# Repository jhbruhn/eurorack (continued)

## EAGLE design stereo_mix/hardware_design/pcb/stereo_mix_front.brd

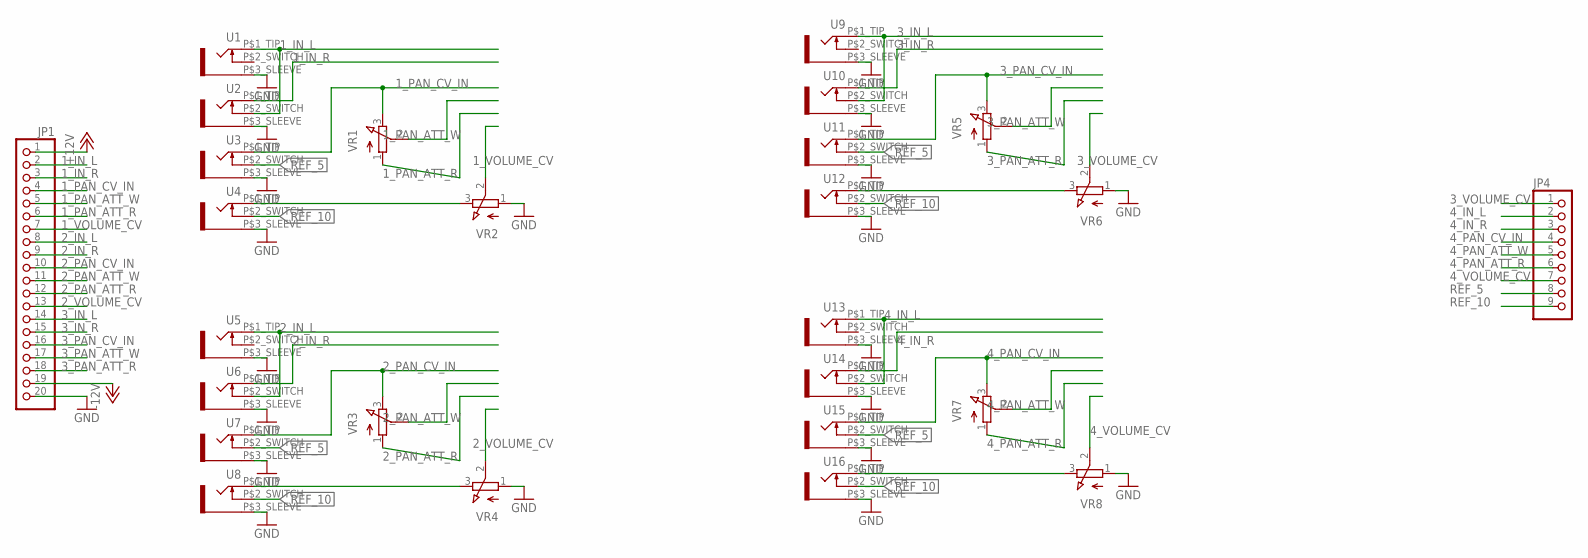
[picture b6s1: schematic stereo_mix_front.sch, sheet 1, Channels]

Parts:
JP1: PINHD-1X20; 1X20
JP4: PINHD-1X9; 1X09
U1, U2, U3, U4, U5, U6, U7, U8, U9, U10, U11, U12, U13, U14, U15, U16: WQP-PJ301M-12_JACK
VR1, VR2, VR3, VR4, VR5, VR6, VR7, VR8: 9MM_SNAP-IN_POT_; 9MM_SNAP-IN_POT

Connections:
1_IN_L: JP1.2, U1.P$1_TIP (2), U2.P$2_SWITCH (3)
1_IN_R: JP1.3, U2.P$1_TIP (2)
1_PAN_ATT_R: JP1.6, VR1.1 (A)
1_PAN_ATT_W: JP1.5, VR1.2 (S)
1_PAN_CV_IN: JP1.4, U3.P$1_TIP (2), VR1.3 (E)
1_VOLUME_CV: JP1.7, VR2.2 (S)
2_IN_L: JP1.8, U5.P$1_TIP (2), U6.P$2_SWITCH (3)
2_IN_R: JP1.9, U6.P$1_TIP (2)
2_PAN_ATT_R: JP1.12, VR3.1 (A)
2_PAN_ATT_W: JP1.11, VR3.2 (S)
2_PAN_CV_IN: JP1.10, U7.P$1_TIP (2), VR3.3 (E)
2_VOLUME_CV: JP1.13, VR4.2 (S)
3_IN_L: JP1.14, U9.P$1_TIP (2), U10.P$2_SWITCH (3)
3_IN_R: JP1.15, U10.P$1_TIP (2)
3_PAN_ATT_R: JP1.18, VR5.1 (A)
3_PAN_ATT_W: JP1.17, VR5.2 (S)
3_PAN_CV_IN: JP1.16, U11.P$1_TIP (2), VR5.3 (E)
3_VOLUME_CV: JP4.1, VR6.2 (S)
4_IN_L: JP4.2, U13.P$1_TIP (2), U14.P$2_SWITCH (3)
4_IN_R: JP4.3, U14.P$1_TIP (2)
4_PAN_ATT_R: JP4.6, VR7.1 (A)
4_PAN_ATT_W: JP4.5, VR7.2 (S)
4_PAN_CV_IN: JP4.4, U15.P$1_TIP (2), VR7.3 (E)
4_VOLUME_CV: JP4.7, VR8.2 (S)
+12V: JP1.1
-12V: JP1.19
GND: JP1.20, U1.P$3_SLEEVE (1), U2.P$3_SLEEVE (1), U3.P$3_SLEEVE (1), U4.P$3_SLEEVE (1), U5.P$3_SLEEVE (1), U6.P$3_SLEEVE (1), U7.P$3_SLEEVE (1), U8.P$3_SLEEVE (1), U9.P$3_SLEEVE (1), U10.P$3_SLEEVE (1), U11.P$3_SLEEVE (1), U12.P$3_SLEEVE (1), U13.P$3_SLEEVE (1), U14.P$3_SLEEVE (1), U15.P$3_SLEEVE (1), U16.P$3_SLEEVE (1), VR2.1 (A), VR4.1 (A), VR6.1 (A), VR8.1 (A); also elsewhere on the board
unnamed: U8.P$1_TIP (2), VR4.3 (E)
unnamed: U4.P$1_TIP (2), VR2.3 (E)
unnamed: U12.P$1_TIP (2), VR6.3 (E)
unnamed: U16.P$1_TIP (2), VR8.3 (E)
REF_5: JP4.8, U3.P$2_SWITCH (3), U7.P$2_SWITCH (3), U11.P$2_SWITCH (3), U15.P$2_SWITCH (3)
REF_10: JP4.9, U4.P$2_SWITCH (3), U8.P$2_SWITCH (3), U12.P$2_SWITCH (3), U16.P$2_SWITCH (3)

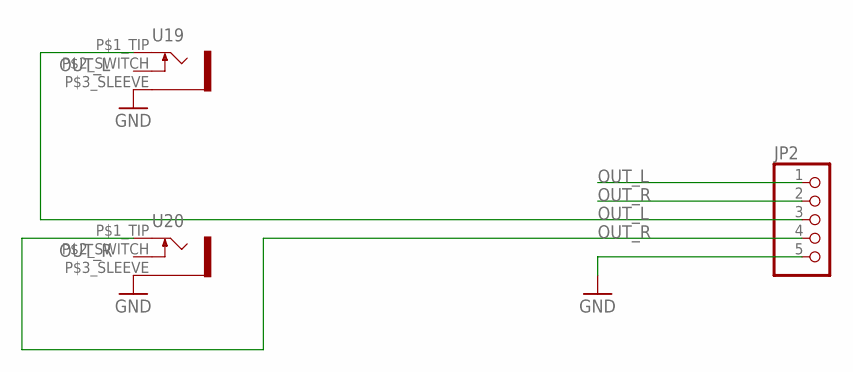
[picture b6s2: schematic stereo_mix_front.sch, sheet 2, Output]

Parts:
JP2: PINHD-1X5; 1X05
U19, U20: WQP-PJ301M-12_JACK

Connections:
GND: JP2.5, U19.P$3_SLEEVE (1), U20.P$3_SLEEVE (1); also elsewhere on the board
OUT_L: JP2.1, JP2.3, U19.P$1_TIP (2)
OUT_R: JP2.2, JP2.4, U20.P$1_TIP (2)

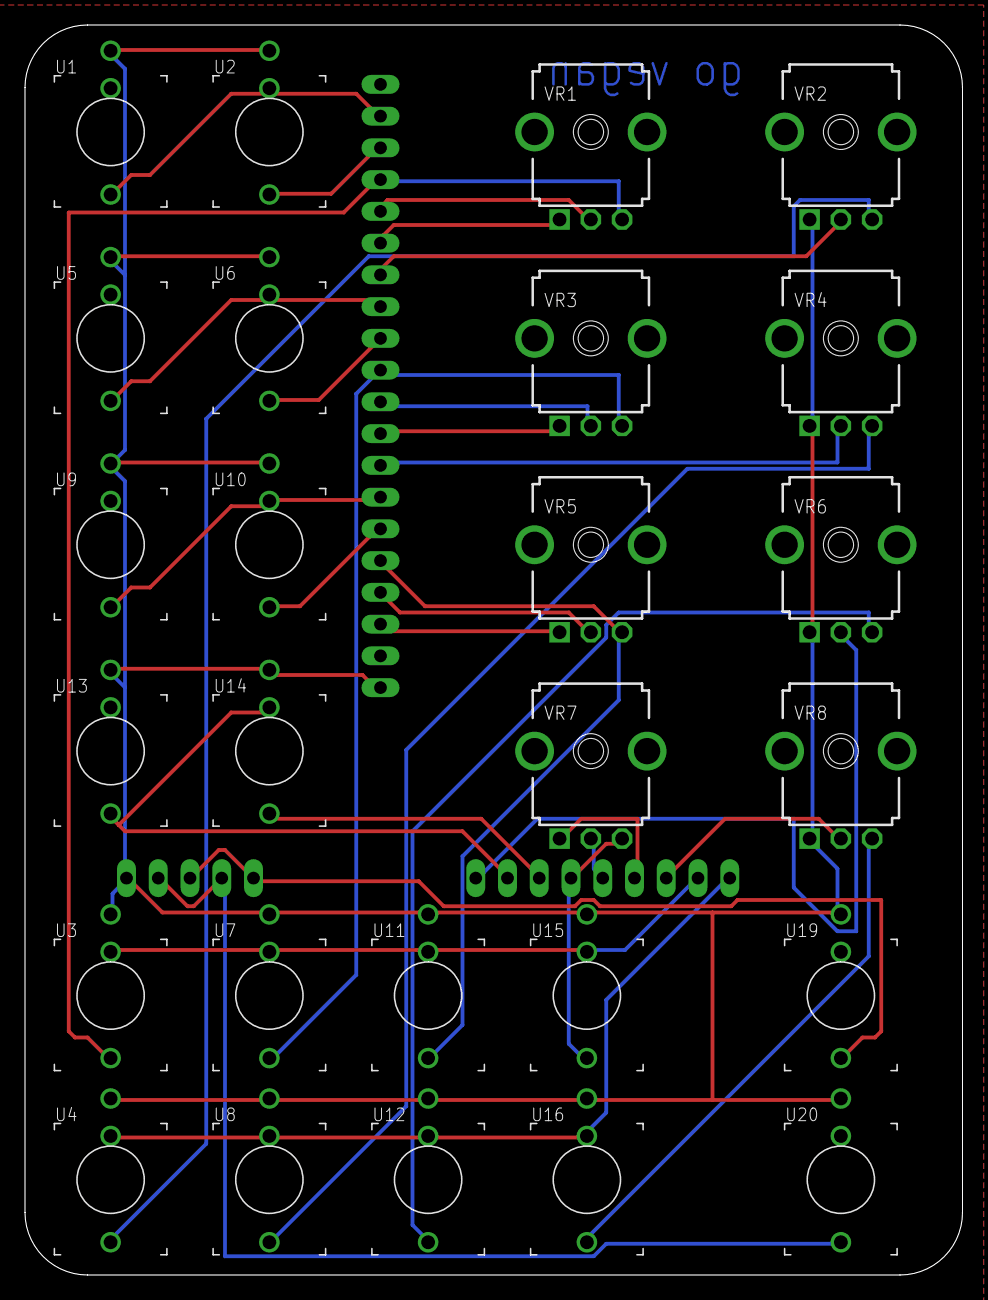
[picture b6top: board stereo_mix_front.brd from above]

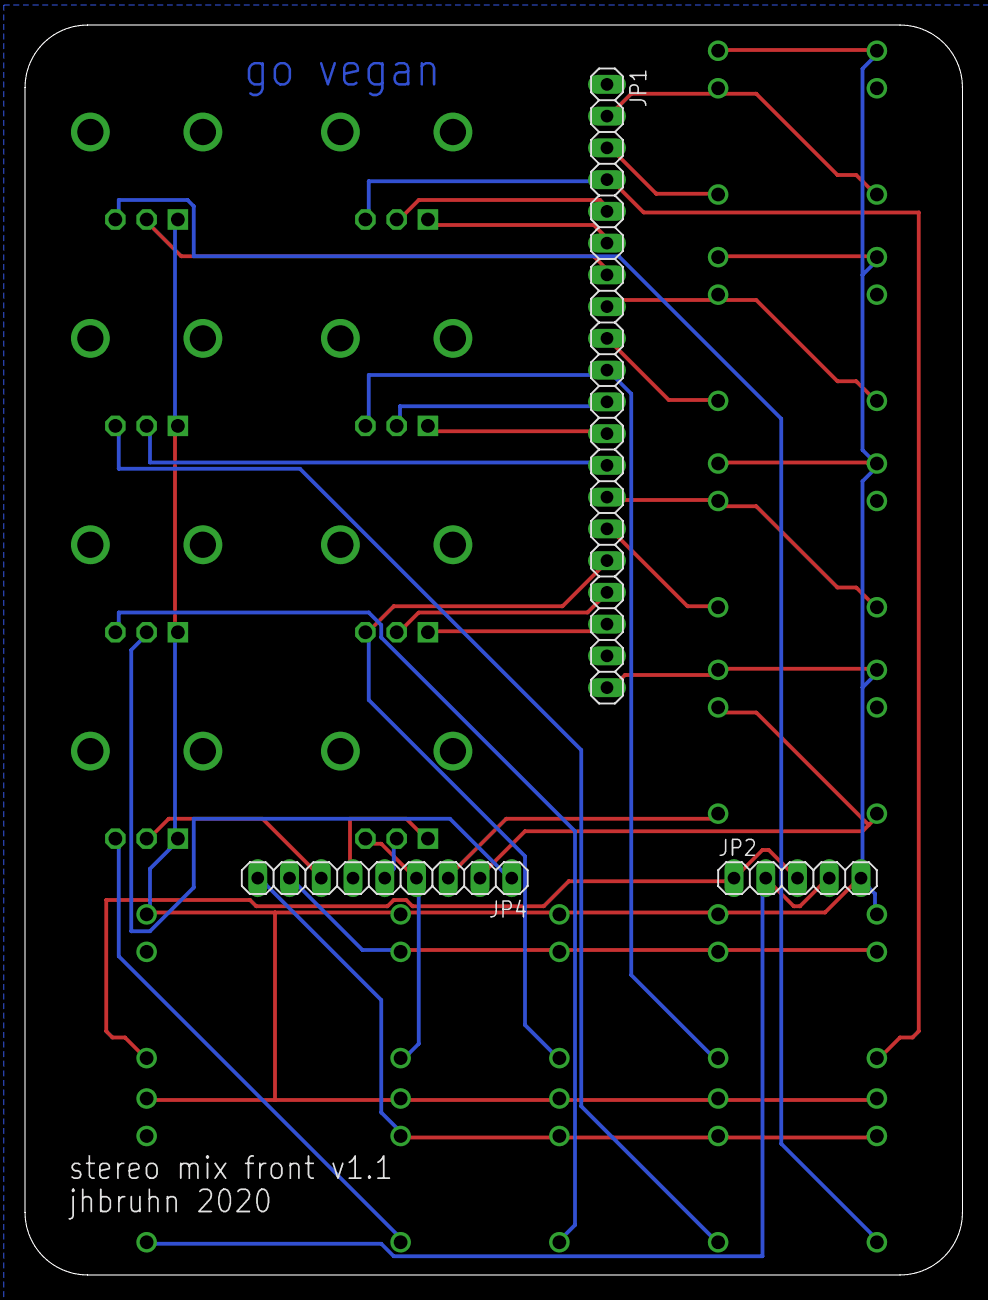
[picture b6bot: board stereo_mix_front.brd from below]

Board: 2 copper layers, 75.0 x 100.0 mm, 29 parts (3 on the bottom side), 33 nets.

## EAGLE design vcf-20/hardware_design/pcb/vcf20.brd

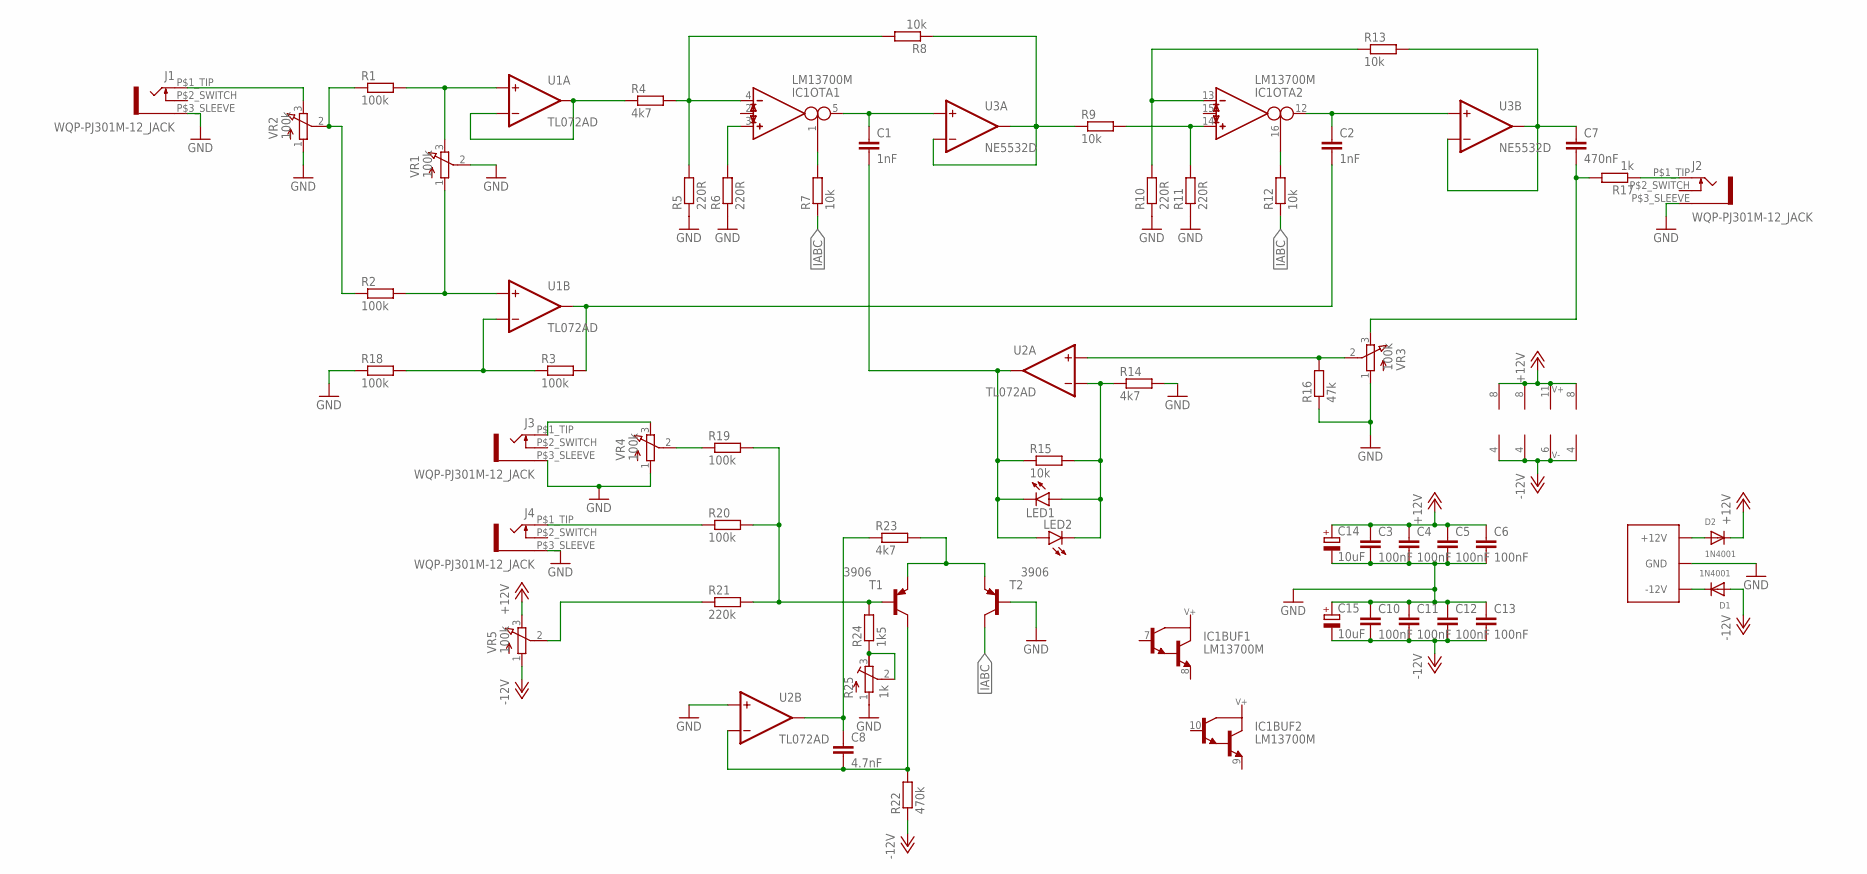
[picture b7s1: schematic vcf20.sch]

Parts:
C1, C2: 1nF; C0402
C3, C4, C5, C6, C10, C11, C12, C13: 100nF; C0402
C7: 470nF; C0402
C8: 4.7nF; C0402
C9: EURO_POWER_LOCKFAT-LOCK; EURO_PWR_HEADER_LOCK
C14, C15: 10uF; PANASONIC_C
D1, D2: 1N4001; SMADIODE
IC1: LM13700M; SO16
J1, J2, J3, J4: WQP-PJ301M-12_JACK
LED1, LED2: LEDSML0603; SML0603
R1, R2, R3, R18, R19, R20: 100k; R0402
R4, R14, R23: 4k7; R0402
R5, R6, R10, R11: 220R; R0402
R7, R8, R9, R12, R13, R15: 10k; R0402
R16: 47k; R0402
R17: 1k; R0402
R21: 220k; R0402
R22: 470k; R0402
R24: 1k5; R0402
R25: 1k; RTRIM64W
T1, T2: 3906; SOT23-BEC
U1, U2: TL072AD; SOIC8
U3: NE5532D; SOIC8
VR1, VR2, VR3, VR4, VR5: 100k; 9MM_SNAP-IN_POT

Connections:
+12V: C3.1, C4.1, C5.1, C6.1, C14.+, D2.C, IC1.11 (V+), U1.8 (V+), U2.8 (V+), U3.8 (V+), VR5.3 (E)
-12V: C10.2, C11.2, C12.2, C13.2, C15.-, D1.A, IC1.6 (V-), R22.1, U1.4 (V-), U2.4 (V-), U3.4 (V-), VR5.1 (A)
GND: C3.2, C4.2, C5.2, C6.2, C9.GND1 (GND), C9.GND2 (GND), C9.GND3 (GND), C9.GND4 (GND), C9.GND5 (GND), C9.GND6 (GND), C10.1, C11.1, C12.1, C13.1, C14.-, C15.+, J1.P$3_SLEEVE (1), J2.P$3_SLEEVE (1), J3.P$3_SLEEVE (1), J4.P$3_SLEEVE (1), R5.1, R6.1, R10.1, R11.1, R14.2, R16.1, R18.1, R25.1 (A), T2.B, U2.5 (+IN), VR1.2 (S), VR2.1 (A), VR3.1 (A), VR4.1 (A)
IABC: R7.1, R12.1, T2.C
unnamed: IC1.4 (IN_N), R4.2, R5.2, R8.2
unnamed: IC1.3 (IN_P), R6.2
unnamed: IC1.1 (I_BIAS), R7.2
unnamed: IC1.14 (IN_P), R9.2, R11.2
unnamed: IC1.16 (I_BIAS), R12.2
unnamed: IC1.13 (IN_N), R10.2, R13.1
unnamed: R8.1, R9.1, U3.1 (OUT), U3.2 (-IN)
unnamed: C1.1, IC1.5 (OUT), U3.3 (+IN)
unnamed: R3.1, R18.2, U1.6 (-IN)
unnamed: C7.1, R13.2, U3.6 (-IN), U3.7 (OUT)
unnamed: C2.1, IC1.12 (OUT), U3.5 (+IN)
unnamed: C2.2, R3.2, U1.7 (OUT)
unnamed: R1.2, U1.3 (+IN), VR1.3 (E)
unnamed: R2.2, U1.5 (+IN), VR1.1 (A)
unnamed: C7.2, R17.2, VR3.3 (E)
unnamed: R4.1, U1.1 (OUT), U1.2 (-IN)
unnamed: R1.1, R2.1, VR2.2 (S)
unnamed: LED1.A, LED2.C, R14.1, R15.2, U2.2 (-IN)
unnamed: J1.P$1_TIP (2), VR2.3 (E)
unnamed: R16.2, U2.3 (+IN), VR3.2 (S)
unnamed: C1.2, LED1.C, LED2.A, R15.1, U2.1 (OUT)
unnamed: J2.P$1_TIP (2), R17.1
unnamed: R24.1, R25.2 (S), R25.3 (E)
unnamed: C8.2, R22.2, T1.C, U2.6 (-IN)
unnamed: J3.P$1_TIP (2), VR4.3 (E)
unnamed: J4.P$1_TIP (2), R20.1
unnamed: R19.1, VR4.2 (S)
unnamed: R21.1, VR5.2 (S)
unnamed: R19.2, R20.2, R21.2, R24.2, T1.B
unnamed: C9.POS1 (+12V), C9.POS2 (+12V), D2.A
unnamed: R23.2, T1.E, T2.E
unnamed: C8.1, R23.1, U2.7 (OUT)
unnamed: C9.NEG1 (-12V), C9.NEG2 (-12V), D1.C

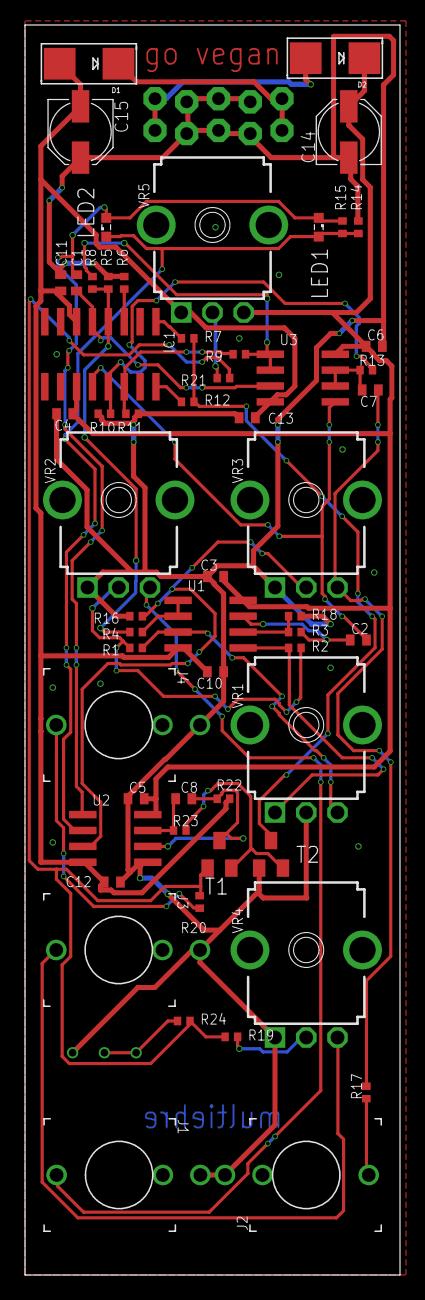
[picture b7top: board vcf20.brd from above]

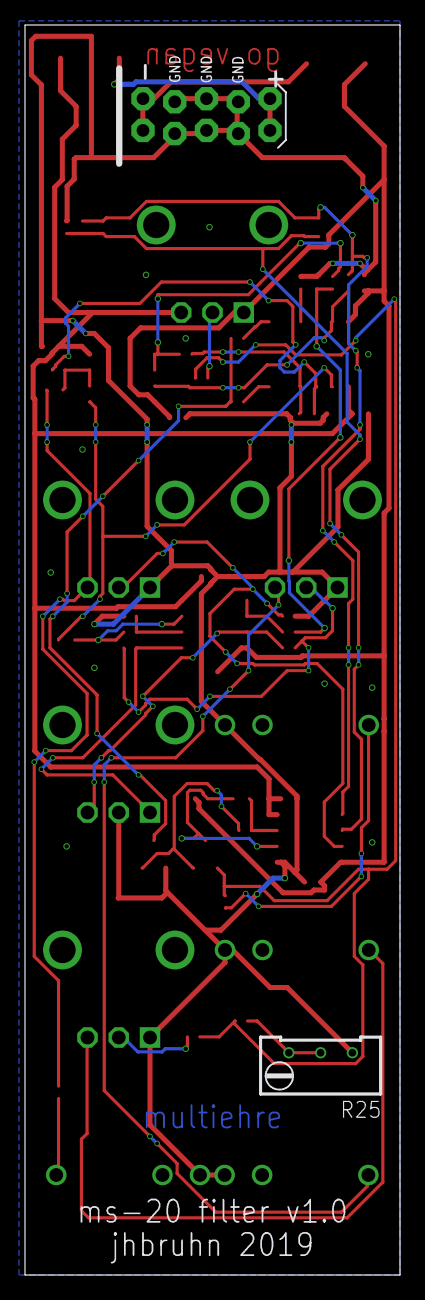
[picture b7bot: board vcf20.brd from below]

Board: 2 copper layers, 30.0 x 100.0 mm, 59 parts (2 on the bottom side), 37 nets.

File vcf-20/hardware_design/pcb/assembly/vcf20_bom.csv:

"Comment","Designator","Footprint","LCSC Part #","LCSC Part Type"
"","LED1, LED2","SML0603","",""
"100k","VR1, VR2, VR3, VR4, VR5","9MM_SNAP-IN_POT","",""
"100k","R1, R2, R3, R18, R19, R20","0402_R","",""
"100nF","C3, C4, C5, C6, C10, C11, C12, C13","0402_C","",""
"10k","R7, R8, R9, R12, R13, R15","0402_R","",""
"10uF","C14, C15","PANASONIC_C","",""
"1N4001","D1, D2","SMADIODE","",""
"1k","R17","0402_R","",""
"1k","R25","RTRIM64W","",""
"1k5","R24","0402_R","",""
"1nF","C1, C2","0402_C","",""
"220R","R5, R6, R10, R11","0402_R","",""
"220k","R21","0402_R","",""
"3904","T1, T2","SOT23-BEC","",""
"4.7nF","C8","0402_C","",""
"470k","R22","0402_R","",""
"470nF","C7","0402_C","",""
"47k","R16","0402_R","",""
"4k7","R4, R14, R23","0402_R","",""
"EURO_POWER_LOCKFAT-LOCK","C9","EURO_PWR_HEADER_LOCK","",""
"LM13700M","IC1","SO16","",""
"NE5532D","U3","SOIC8","",""
"TL072AD","U1, U2","SOIC8","",""
"WQP-PJ301M-12_JACK","J1, J2, J3, J4","WQP-PJ301M-12_JACK","",""

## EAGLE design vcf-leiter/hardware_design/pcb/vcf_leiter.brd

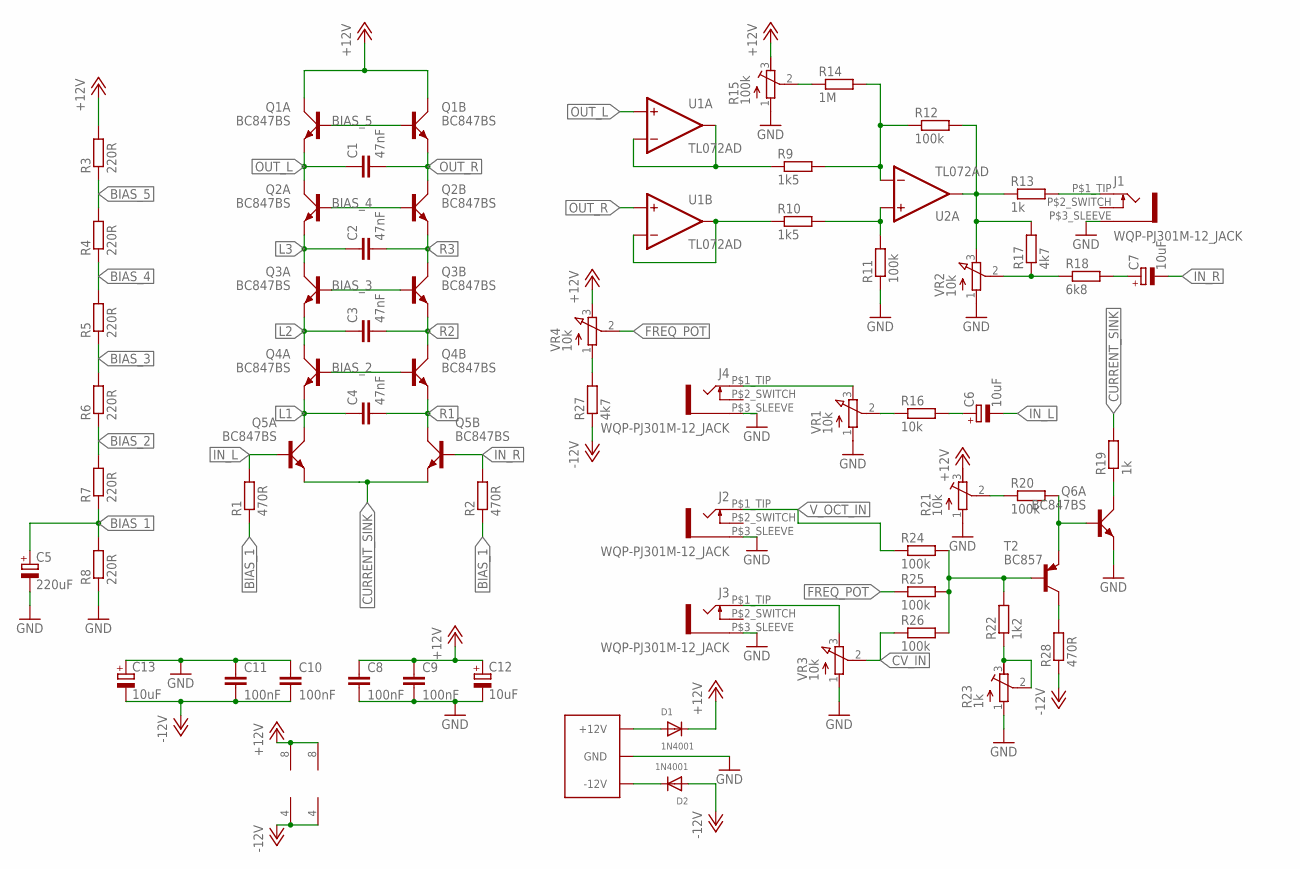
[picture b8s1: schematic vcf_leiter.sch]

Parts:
C1, C2, C3, C4: 47nF; C0402
C5: 220uF; PANASONIC_C
C6, C7, C12, C13: 10uF; PANASONIC_C
C8, C9, C10, C11: 100nF; C0402
C14: EURO_POWER_LOCKFAT-LOCK; EURO_PWR_HEADER_LOCK
D1, D2: 1N4001; SMADIODE
J1, J2, J3, J4: WQP-PJ301M-12_JACK
Q1, Q2, Q3, Q4, Q5, Q6: BC847BS; SOT363_PHILIPS
R1, R2, R28: 470R; R0402
R3, R4, R5, R6, R7, R8: 220R; R0402
R9, R10: 1k5; R0402
R11, R12, R20, R24, R25, R26: 100k; R0402
R13, R19: 1k; R0402
R14: 1M; R0402
R15: 100k; RTRIM64W
R16: 10k; R0402
R17, R27: 4k7; R0402
R18: 6k8; R0402
R21: 10k; RTRIM64W
R22: 1k2; R0402
R23: 1k; RTRIM64W
T2: BC857; SOT23-BEC
U1, U2: TL072AD; SOIC8
VR1, VR2, VR3, VR4: 10k; 9MM_SNAP-IN_POT

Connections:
+12V: C8.1, C9.1, C12.+, D1.C, Q1.3 (C), Q1.6 (C), R3.2, R15.3 (E), R21.3 (E), U1.8 (V+), U2.8 (V+), VR4.3 (E)
-12V: C10.2, C11.2, C13.-, D2.A, R27.1, R28.1, U1.4 (V-), U2.4 (V-)
BIAS_1: C5.+, R1.1, R2.1, R7.1, R8.2
BIAS_2: Q4.2 (B), Q4.5 (B), R6.1, R7.2
BIAS_3: Q3.2 (B), Q3.5 (B), R5.1, R6.2
BIAS_4: Q2.2 (B), Q2.5 (B), R4.1, R5.2
BIAS_5: Q1.2 (B), Q1.5 (B), R3.1, R4.2
CURRENT_SINK: Q5.1 (E), Q5.4 (E), R19.2
CV_IN: R26.1, VR3.2 (S)
FREQ_POT: R25.1, VR4.2 (S)
GND: C5.-, C8.2, C9.2, C10.1, C11.1, C12.-, C13.+, C14.GND1 (GND), C14.GND2 (GND), C14.GND3 (GND), C14.GND4 (GND), C14.GND5 (GND), C14.GND6 (GND), J1.P$3_SLEEVE (1), J2.P$3_SLEEVE (1), J3.P$3_SLEEVE (1), J4.P$3_SLEEVE (1), Q6.1 (E), R8.1, R11.1, R15.1 (A), R21.1 (A), R23.1 (A), VR1.1 (A), VR2.1 (A), VR3.1 (A)
IN_L: C6.-, Q5.2 (B), R1.2
IN_R: C7.-, Q5.5 (B), R2.2
L1: C4.1, Q4.1 (E), Q5.6 (C)
L2: C3.1, Q3.1 (E), Q4.6 (C)
L3: C2.1, Q2.1 (E), Q3.6 (C)
unnamed: R9.1, U1.1 (OUT), U1.2 (-IN)
unnamed: R10.1, U1.6 (-IN), U1.7 (OUT)
unnamed: R10.2, R11.2, U2.3 (+IN)
unnamed: R9.2, R12.1, R14.2, U2.2 (-IN)
unnamed: J4.P$1_TIP (2), VR1.3 (E)
unnamed: R12.2, R13.1, R17.2, U2.1 (OUT), VR2.3 (E)
unnamed: R14.1, R15.2 (S)
unnamed: R16.1, VR1.2 (S)
unnamed: C6.+, R16.2
unnamed: J1.P$1_TIP (2), R13.2
unnamed: R17.1, R18.1, VR2.2 (S)
unnamed: C7.+, R18.2
unnamed: Q6.2 (B), R20.2, T2.E
unnamed: J3.P$1_TIP (2), VR3.3 (E)
unnamed: Q6.6 (C), R19.1
unnamed: R20.1, R21.2 (S)
unnamed: R22.2, R24.2, R25.2, R26.2, T2.B
unnamed: R22.1, R23.2 (S), R23.3 (E)
unnamed: R27.2, VR4.1 (A)
unnamed: R28.2, T2.C
unnamed: C14.POS1 (+12V), C14.POS2 (+12V), D1.A
unnamed: C14.NEG1 (-12V), C14.NEG2 (-12V), D2.C
OUT_L: C1.1, Q1.1 (E), Q2.6 (C), U1.3 (+IN)
OUT_R: C1.2, Q1.4 (E), Q2.3 (C), U1.5 (+IN)
R1: C4.2, Q4.4 (E), Q5.3 (C)
R2: C3.2, Q3.4 (E), Q4.3 (C)
R3: C2.2, Q2.4 (E), Q3.3 (C)
V_OCT_IN: J2.P$1_TIP (2), R24.1

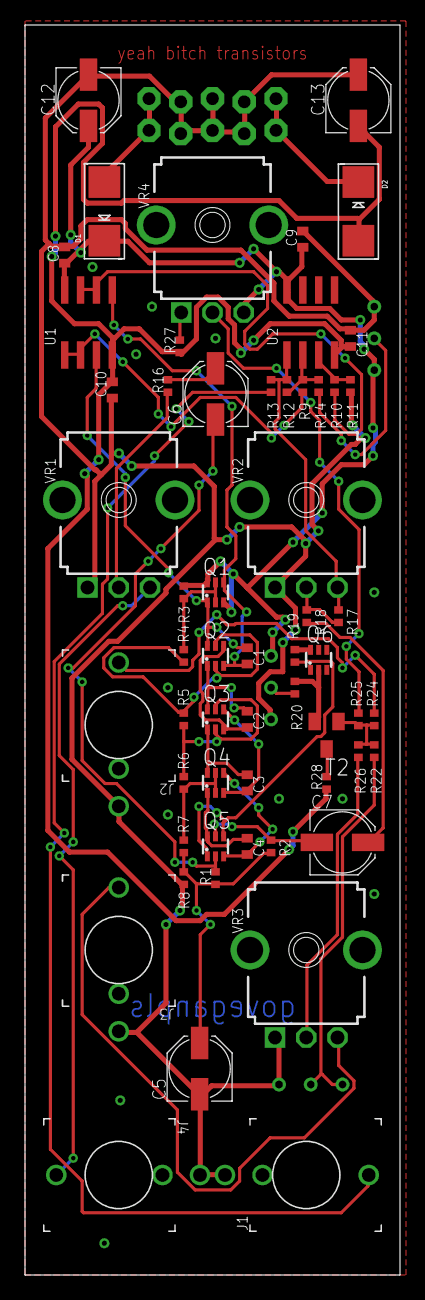
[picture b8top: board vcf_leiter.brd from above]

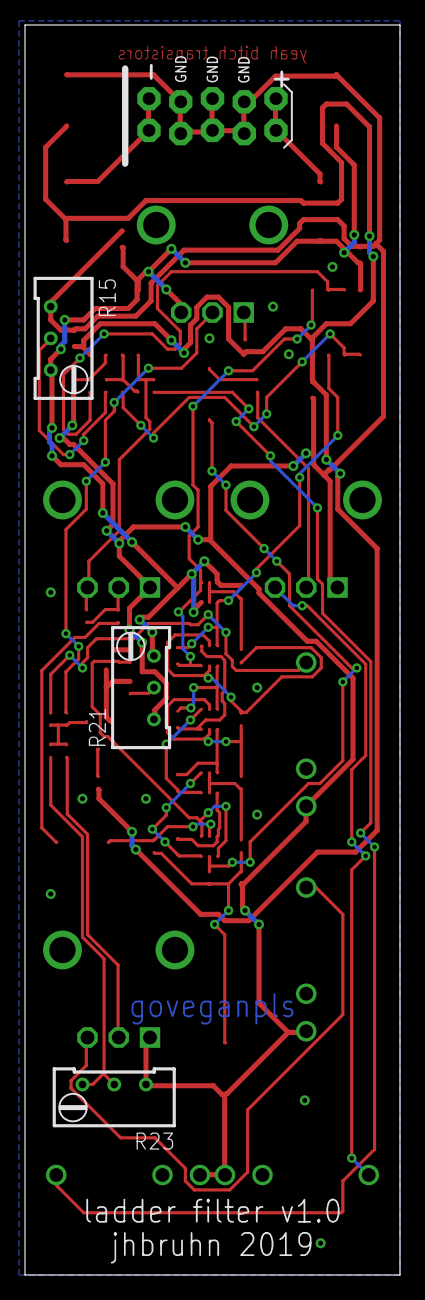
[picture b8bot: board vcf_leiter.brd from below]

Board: 2 copper layers, 30.0 x 100.0 mm, 61 parts (4 on the bottom side), 44 nets.

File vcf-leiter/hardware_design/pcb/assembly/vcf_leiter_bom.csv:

"Comment","Designator","Footprint","LCSC Part #","LCSC Part Type"
"100k","R11, R12, R20, R24, R25, R26","0402_R","",""
"100k","R15","RTRIM64W","",""
"100nF","C8, C9, C10, C11","0402_C","",""
"10k","VR1, VR2, VR3, VR4","9MM_SNAP-IN_POT","",""
"10k","R16","0402_R","",""
"10k","R21","RTRIM64W","",""
"10uF","C6, C7, C12, C13","PANASONIC_C","",""
"1M","R14","0402_R","",""
"1N4001","D1, D2","SMADIODE","",""
"1k","R13, R19","0402_R","",""
"1k","R23","RTRIM64W","",""
"1k2","R22","0402_R","",""
"1k5","R9, R10","0402_R","",""
"220R","R3, R4, R5, R6, R7, R8","0402_R","",""
"220uF","C5","PANASONIC_C","",""
"470R","R1, R2, R28","0402_R","",""
"47nF","C1, C2, C3, C4","0402_C","",""
"4k7","R17, R27","0402_R","",""
"6k8","R18","0402_R","",""
"BC847BS","Q1, Q2, Q3, Q4, Q5, Q6","SOT363_PHILIPS","",""
"BC857","T2","SOT23-BEC","",""
"EURO_POWER_LOCKFAT-LOCK","C14","EURO_PWR_HEADER_LOCK","",""
"TL072AD","U1, U2","SOIC8","",""
"WQP-PJ301M-12_JACK","J1, J2, J3, J4","WQP-PJ301M-12_JACK","",""

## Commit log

2018-10-23 Add code
2018-11-14 Update hardware design
2018-11-15 Fix Scaling Issues
2018-11-15 Use different one-hot to binary encoder
2018-11-15 Add USB Interface (completely untested)
2018-11-15 Specify USB Host Clock Frequency
2019-07-29 First Revision
2019-08-08 Rev 1/2
2019-08-19 Update folder structure
2019-08-19 Update submodule
2019-08-20 Add VCA2 beta, empty midi2cv program
2019-08-20 Update gitingo
2019-08-20 Add other, less cool VCA based on MFOS design
2019-08-26 Add stereo mix proto
2019-08-26 Simulate a panner/volume VCA
2019-08-29 Start implementation of stereo_mixer
2019-08-29 show more layers for midi
2019-08-29 Add empty bootloader
2019-08-30 Start driver implementation
2019-08-30 Fix build process to work, implement bootloader that does nothing
2019-09-02 start stereo mix board layout. big oof
2019-09-02 Use newer processor for midi2cv, fix some hardware mistakes
2019-09-02 Try to implement a display driver (but failed). hardware problem? new processor incoming anyways
2019-09-02 Use some sweet ass voltage references
2019-09-02 Last layout improvements
2019-09-07 Update midi board layout
2019-09-07 Make stereo mix a two layer board
2019-09-07 Add U8G2 to midi2cv. Start port to stm32f373
2019-09-08 Add readme
2019-09-08 Fix readme heading
2019-09-09 Add tools
2019-09-19 Display driver fixes, UI
2019-09-19 Implement double buffering for screen, only do transmission in interrupt handler
2019-09-19 Improve switiching between spi modes
2019-10-04 Add custom vim config
2019-10-04 Start Part class
2019-10-04 Rename BiOutputMode oscillator types
2019-10-06 Create Part class, think about output assignments
2019-10-14 Improve Menu Implementation situation, optimize parameter set for part
2019-10-22 Fix UI Drawing
2019-10-28 Implement ui stuff
2019-11-16 Add stereo mix back digital pcb and tests
2019-11-16 Move hardware design of stereo_mix to proper folder, delete schmaamsch
2019-12-03 Add Initial code for stereo_mix module
2019-12-03 Use my own avrlib
2019-12-03 Fix inttypes import for midi2cv
2019-12-03 Further optimize the codes performance by utilizing luts for the sin/cos
2019-12-03 Remove unused math import
2019-12-05 Add simulations and schematic for next hardware revision, adding the missing variable bias to the opamp after the MDAC
2019-12-09 Add new revision of stereo_mix_back hardware, and associated assembly files
2019-12-16 Add vcf20
2019-12-16 Add ladder filter
2020-01-03 Add menu datastrctures
2020-01-07 Finish stereo mix software (could be further optimized though
2020-01-09 Fix reversed power connector for vcf-20
2020-01-12 Add new version of stereo_mix_front panel
2020-01-12 New version of vca2 with manufacturing parts. This is the first dirty version!!!!!
2020-01-12 Add out-pcb and assembly files.
2020-01-12 Add vcf-20 panel 3d-printing files.
2020-01-12 add vcf-leiter 3d-print panel files
2020-01-12 Update stmlib
2020-01-15 Fix Offset DAC gain being set to 1x instead of 2x. Improve performance of stereo_mix.
2020-02-04 Implement menu rendering (very basic without selection)
2020-02-04 Fix out oderso, implement menu scrolling i guess
2020-02-05 Menu Item Implementation fixes, rendering improvements, implement menu scrolling
2020-02-17 Performance improvements
2020-02-17 Start revamp of stereo mix pcb
2020-02-18 reduce size of stereo mix program (atmega88????), decrease lut resolution, improve volume curve
2020-02-18 Further lut resolution optimizations
2020-02-18 numpy beautification
2020-02-21 Implement editing of values in menus
2020-02-21 Ozone debugger support
2020-02-22 Implement submenus for parts (or at least the ability to have those).
2020-02-22 Implement MidiNote MenuItem
2020-02-22 Implement BoolMenuItem, beautify header
2020-02-23 Remove unnecessary menu consdtructor parameters
2020-02-23 Remove unused visible parameter from menu items, select part 0 as default on boot
2020-02-23 Implement StringListMenuItem
2020-02-23 Update stmlib, remove return value from UI::DoEvents
2020-02-23 Implement Midi Channel select as stringlist, add midi input filter
2020-02-23 Add enum values to part, implement midi thru menu item
2020-02-23 Switch to C++ interface of U8G2.
2020-02-23 Reconfigure display (and dac) driver
2020-02-23 Move menu item values to pointers pointing to the variable to be changed
2020-02-23 Remove ui init function
2020-02-23 Null safety for menu items, remove initialized flag from part_menu
2020-02-24 Implement setting storage, location of data values has to change though...
2020-02-24 Create PartData struct for part to store it in flash
2020-02-24 temporarily disable random part state things
2020-02-25 Implement U8x8 based display support in bootloader.
2020-02-25 Re-Enlarge settings storage, add some tests to bootloader
2020-02-25 Implement funny bootscreen
2020-02-26 Implement invisible menu items but also destroy scrolling
2020-02-26 Fix visible item implementation
2020-02-26 Fix scrolling for invisible items
2020-02-26 Optimize update_visible_items for higher efficiency
2020-02-26 Further optimize update_visible_items
2020-02-26 Fix bug when items are not visible on boot
2020-02-26 Shorten bootscreen
2020-02-26 Move midi filter enabled back to original position
2020-03-02 Add support for libopencm3
2020-03-07 Revert "Add support for libopencm3"
    This reverts commit 266dbb178f1d7c57f5eca562d89b20094394077b.
2020-03-14 Add new hardware revision of stereo mix
2020-03-14 Add SOIC8 hack to mnbtool
2020-03-14 Rename vca2 to vca, remove vca
2020-03-14 Add vca panel
2020-03-14 Port parts of peaks to a pure adsr module
2020-03-14 Implement mini sequencer
2020-03-15 Add fake tides
2020-03-15 Implement some weird wavefolding
2020-03-15 Replace weird nonworking wavefolder with sustain/silence length adjustment
2020-03-27 Add new implementation start of stereo_mix
2020-03-27 Upgrade stmlib
2020-03-29 Fix rotation in mnbtool
2020-03-29 Replace bomtool and mnbtool with ulp script
2020-03-30 Add jlcpcb-eagle submodule, add new resources for stereo_mix
2020-04-01 Basic software prototype of stm32 stereo_mix finished
2020-04-01 Update jlcpcb-eagle
2020-04-03 stereo mix routing nearly finished
2020-04-04 All very important signals routed
2020-04-04 Add new hardware revision
2020-04-04 Update jlcpcb-eagle submodule
2020-04-10 Migrate stereo_mix to HAL
2020-04-10 Add small busboard
2020-04-12 stereo_mix: adc groups
2020-04-13 Use HAL drivers for midi2cv
2020-04-13 Fixes for stereo_mix hal drivers
2020-04-13 move interrupt callbacks to peripherals
2020-04-17 Remove unused files from midi2cv, implement some polyphony related things
2020-04-17 Fix SPI Display transmission bug
2020-04-18 Add draft of AD57X4 driver
2020-04-18 Implement 'smart' setVoltage function
2020-04-18 Fix bug in MidiNoteMenuItem for negative octaves
2020-04-18 Fix bugs in AD57X4 driver implemenation
2020-04-23 Fix problem in stereo_mix dac
2020-04-23 Update stmlib, implement LED softpwm with TIM3
2020-04-23 Remove untrue comment
2020-04-23 Implement gamma correction for volume LED
2020-04-23 Improved gamma handling
2020-04-24 Change gamma value
2020-04-24 Testing Mute switch function
2020-04-25 Implement hidden attenuverters for volume
2020-04-25 Divide ui in different tasks, show values when pots change
2020-04-25 Hardware filtering improvements
2020-04-26 Improve skew calculation
2020-04-26 Move processing code to own processor class.
2020-04-26 Implement timer for output writing, implement CV input
2020-04-26 tremendous spi performance improvements
2020-04-26 Add debug pin
2020-04-27 Remove old stereo mix folder
2020-04-27 Improve dac performance
2020-04-28 Add ability to change response curve of volume CV and volume pot
2020-04-28 Fix overrun bug, implement proper equal power panning
2020-05-09 Implement support for multiple hidden parameters
2020-05-09 Fix values from pots being always passed on to the processor
2020-05-09 Interpolate between lut entries
2020-05-10 Implement attenuverters
2020-05-10 Fixes in processing and attenuverter operation
2020-05-11 Fix onepole filter bug in processor resulting in wrong CV values
2020-07-04 Remove vca from readme
2020-07-16 Update stereo_mix to new hardware revision
2020-07-16 Remove usb from midi
2020-07-16 Add 3d printable front panel
2020-07-16 Fix timer channel bug
2020-07-17 Fix bugs
2020-07-17 Remove old front panel, rename boardfile
2020-07-17 Make space for settings storage
2020-07-17 Make space by reducing useless high resolution led gamma tables
2020-07-17 Update comment
2020-07-19 Add testing bootloader for stereo_mix
2020-07-20 Implement settings storage for stereo_mix
2020-08-16 Improve startup sequence for leds
2020-10-29 Move midi2cv to deprecated folder
2020-10-29 Update jlcpcb-eagle module
2020-10-29 Fix formatting in readme
2020-12-03 Add Clang format spec
2020-12-03 Remove obsolete import
2021-03-13 Add license to readme
